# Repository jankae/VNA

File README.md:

# 1MHz - 6GHz VNA

**There is a [new and improved version](https://github.com/jankae/VNA2) of this project under development**

## Motivation
A VNA can be very helpful for RF experiments so I decided to build one for my next project. I already own a [pocketVNA](https://pocketvna.com/), however I found some issues with it and didn't use it very often:
* High thermal drift: you have to leave it running for 30-45 minutes before using it
* Low sweep speed: Especially with averaging enabled, a sweep can take a few minutes
* Ports are not 50 Ohm terminated, see also discussion [here](https://www.eevblog.com/forum/rf-microwave/pocketvna-any-idea-what-its-like/msg1220143/#msg1220143)

There already are some other DIY VNA projects online, especially [these](https://hforsten.com/cheap-homemade-30-mhz-6-ghz-vector-network-analyzer.html) [two](http://www.yl3akb.lv/content/vna_v2/vna_v2.php) served as inspiration. Especially the first link also explains some general concepts of a VNA, what it is used for, how it works and some compromises when choosing a hardware architecture.

## Design goals
* 1MHz to 6GHz usable frequency range. Both limits are essentially set by the specs of affordable RF ICs.
* Reasonable fast sweep speed
* No display, instead the data is send via USB to a PC. Generally, I prefer standalone devices but it seemed not worth the effort here. To be usable, the display would need to be reasonable large and high resolution, also GUI development is faster/easier on a PC than on a µC.
* BOM cost reduction is *not* the primary goal. A project like this takes several month and its a one-off device, slightly higher than absolutely necessary part costs are not an issue.
* Learn more about the challenges in RF designs.

## How does it work?

* The main clock source is an Si5351C, providing all the required clocks for the different blocks. It also serves as the stimulus source for frequencies below 25MHz. Its own reference clock is either a 26MHz crystal or an external 10MHz signal.
* The stimulus source for frequencies above 25MHz is a MAX2871. Its output signal is slightly filtered to reduce the amount of harmonics.
* The stimulus signal power can be adjusted between approximately -42 and -10dbm with a digital attenuator (F1958).
* After the amplifier(TRF37A73) the signal is split and the weaker part of it fed into the reference receiver.
* The stronger part of the signal can be routed to either port. In each signal path, two RF switches are used in series to achieve higher isolation between the ports.
* Instead of directional couplers, resistive return-loss-bridges are used (easier to implement for wide bandwidth).
* Both ports have completely separated receive paths. This increases BOM cost but allows measuring two parameters at once (S11 and S21 or S22 and S12). It also avoid potential isolation issues that could arise if the receive paths would merge into a single mixer/ADC.
* Each receiver consists of two down-convert mixers. The 1.IF sits at 60MHz, the 2.IF 250kHz.
* The ADCs are sampling the final IF with 16bit@1MHz.
* The acquisition and control of the PLLs, switches, attenuator etc. is handled by a Spartan 6 FPGA. This allows for nearly instant switching of the measurement frequency, only limited by the settling time of the PLLs.

## PCB Layout
The signal path can also be followed on the PCB (the attuator is replaced by a wire bridge in this picture because I damaged the IC during soldering):

* I limited myself to 10x10cm, because larger 4-Layer PCBs are getting a bit more expensive at the typical manufacturers. This was a mistake because it meant that certain sections had to move closer together. Especially the distance between the HF Source and the 1.Mixer of Port 1 is not sufficient, resulting in less than optimal isolation.
* The individual sections are divided by strips of exposed GND. The aluminium case touches all the exposed copper and further improves shielding. I expected the shielding to be better than it turned out, this is another reason why I put sections close to each other that really should be some distance apart.
* For some reason I didn't check the final design carefully enough before ordering and didn't have enough GND vias in quite a few areas. This probably degrades overall performance but I am not going to reorder (and solder!) a new PCB.

### Some hardware-related points worth noting
* There is a lot of local voltage regulation to prevent coupling of supply noise between the sections. In total there are 14 different supply rails (although most of them are at 3.3V or 5V).
* The triple Buck converter for stepping down the main 12V input rail to 6V/3V3 and 1V8 has a synchronisation feature. The synchronization pin was connected to the FPGA in order to sync the converter to the ADC sampling rate and prevent switching noise from being measured. I ended up having to cut that trace because the Spartan 6 switches its pins to pullups while being configured from the ISE IDE. This caused the buck converter to stop and the board to lose power. Note that the HSWAPEN pin only affects the pullups when configuring from the *Flash* not from the IDE. See also [this](https://forums.xilinx.com/t5/Spartan-Family-FPGAs-Archived/Spartan-6-pull-ups-during-SPI-indirect-programming-using/td-p/201743) issue. The missing synchronisation ended up not being a problem as the buck converter frequency is far enough away from the final IF.
* Due to 16bit resolution at 1MSPS, the ADCs need a fast SPI interface. Initially I used a 100MHz SPI clock and this worked well for the port 1 and the reference ADC but didn't work with the port 2 ADC (it is farther away from the FPGA thus the traces were longer). Decreasing the SPI clock to about 70MHz solved the issue while still being fast enough for the ADCs.
* The LTC5510 mixers and MAX2871 PLLs get warm (overall power consumption is about 6W, most of it dissipated in these ICs), they reached up to 70°C with an ambient temperature of 25°C. I changed the aluminium shielding design to extend down to these ICs and also serve as a heatsink. This reduced the maximum temperature by about 20°C.

## The shielding

The shielding serves multiple purposes:
* Providing RF isolation between different sections
* Improving EMI/EMC
* Serving as a case for the device, preventing shorts on the PCB when used on the bench
* Cooling (the black rectangles on the left aluminium part are adhesive cooling pads and touch the top of some ICs)
* It was CNC-machined out of 6mm aluminium. Being able to use a CNC mill, I wasn't restricted to right angles and optimised the shielding to allow for a smaller board.

## PC Software

* Written in Qt. This was my first PC software with a GUI and it took a while (and many lines of code that were rewritten a lot) to understand the concepts. While certainly not optimal, the result is absolutely usable for me.
* Flexible display of measurements in charts (Smithchart/Bodeplot). Each chart can be assigned a number of traces (e.i. plot S22 and S11 in one smithchart). The charts can be resized, moved, deleted or split into more charts.
* Import/export of touchstone files up to 4 ports. This allows saving measurements and also comparing the current measurement with others.
* Rudimentary marker system to read S-parameters at any frequency.
* Full control over start/center/stop frequencies, span, IF bandwidth, number of points, stimulus power level, ...
* SOLT calibration with fully customizable calibration kit (either from coefficients or touchstone measurements):

* Manually control of the hardware components (helpful for hardware debugging or using the device as a simple signal source):

## How well does it work?
I am really not that sure, as I have no RF equipment to compare it to. A VNA can only be as good as the calibration kit and the only calibration kit I have is the on that came with the pocketVNA, which does not have any calibration coefficients. Why is that a problem? No calibration kit is perfect and the coefficients allow the VNA to take the imperfections into account. Without the coefficients these imperfections will be propagated to the measurements. As calibration kits with coefficients easily cost more than this whole project (at least the ones I could find) this situation will probably not change soon.

That being said, here are a few measurements:
* Isolation between ports with (green) and without (red) shielding (1MHz to 6GHz, 501 points, 100Hz IF bandwidth, both ports terminated into 50 Ohm):
  * S12:
  
  * S21:
  
  * Below about 1GHz the noise floor is the actual noise floor of the ADC. Above 1GHz more and more signal leaks into the other port. This leakage is a bit worse at port 1 (S12) because the HF source is placed close to the port 1 mixers. The shielding improves the isolation somewhat but not to the extend I had hoped. Interestingly there are some peaks in the isolation sweep when the shielding is used. My best guess is that they are caused by the cavities in the shielding acting as waveguides. I am hoping to improve the shielding by adding RF absorbers to some parts of the aluminium.
* The cavity bandpass filter from [this](https://github.com/jankae/SpectrumAnalyzer) project (1.9GHz to 2.3GHz, 501 points, 1kHz IF bandwidth):
 
* A WLAN antenna that seems to be somewhat reasonable matched between 2.3GHz and 2.6GHz:

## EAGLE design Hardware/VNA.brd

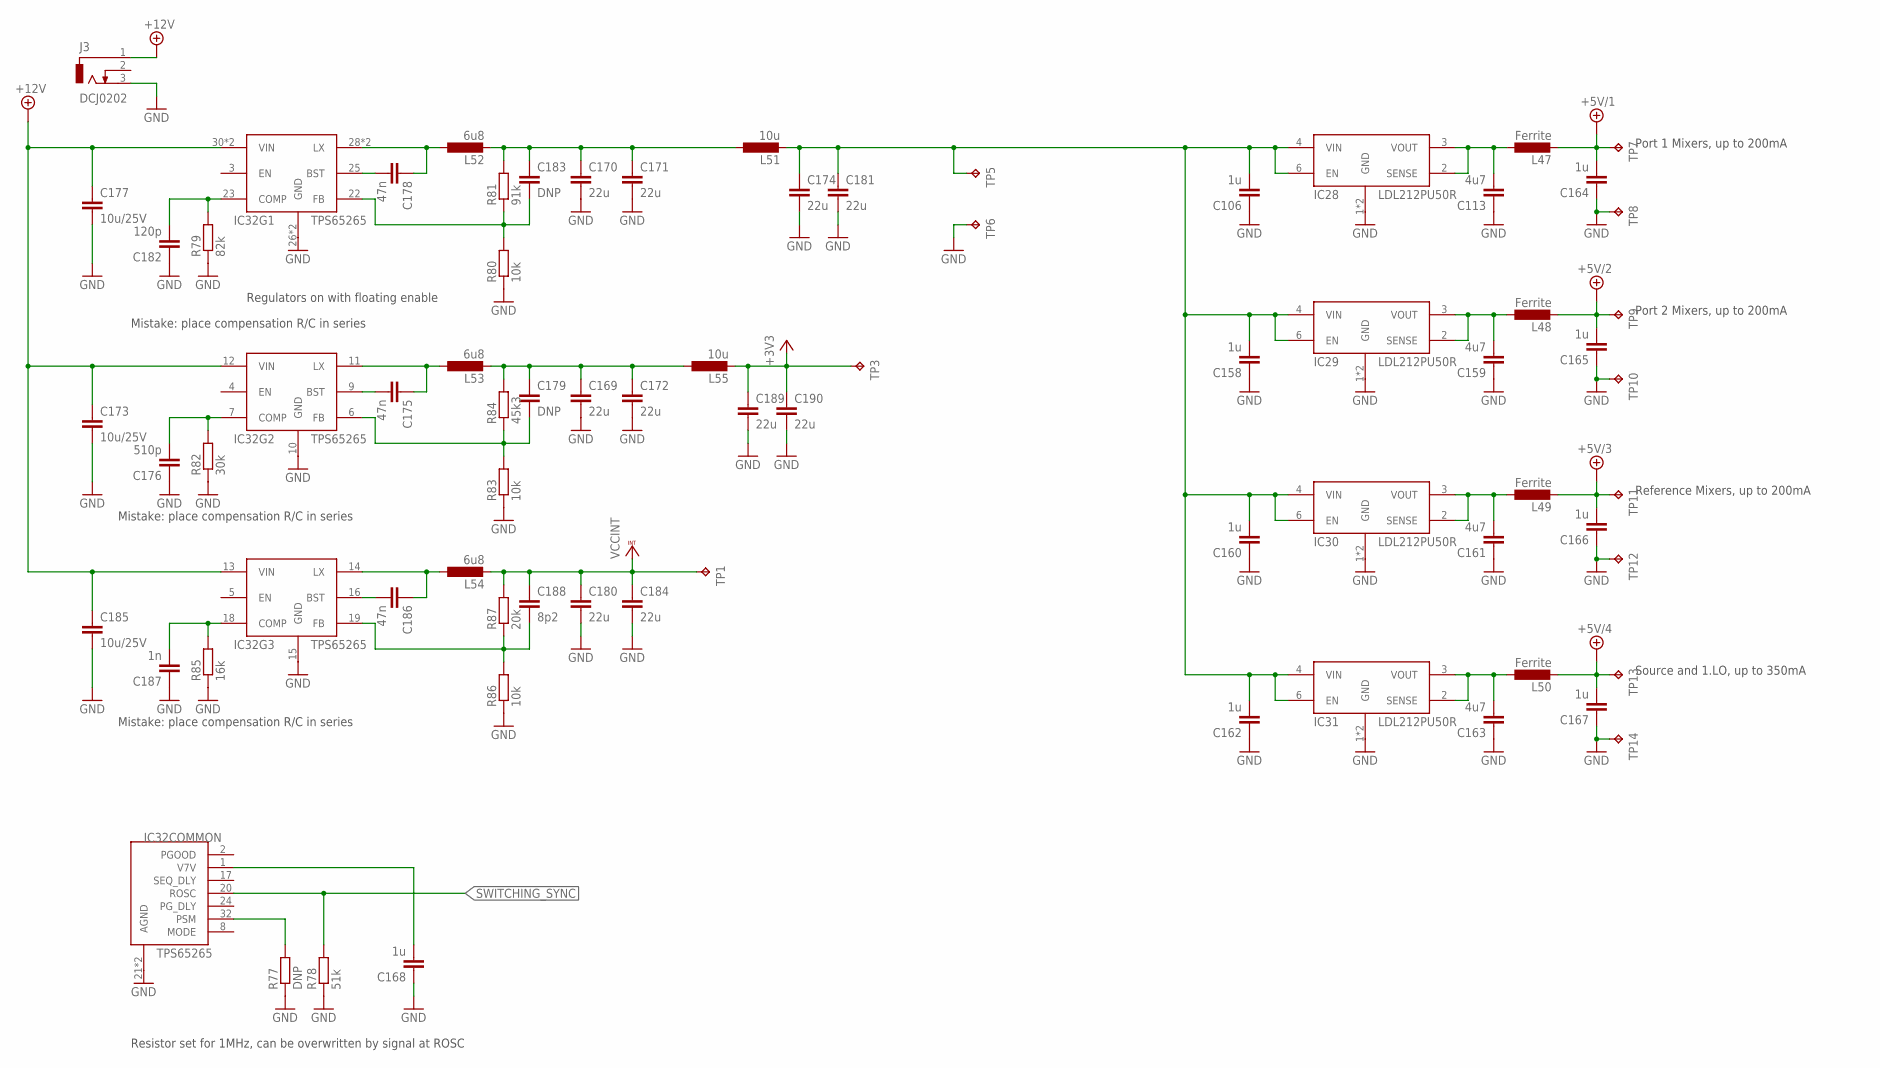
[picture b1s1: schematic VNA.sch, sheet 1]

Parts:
C106, C158, C160, C162, C164, C165, C166, C167, C168: 1u; C0603
C113, C159, C161, C163: 4u7; C0603
C169, C170, C171, C172, C174, C180, C181, C184, C189, C190: 22u; C1206
C173, C177, C185: 10u/25V; C1206
C175, C178, C186: 47n; C0603
C176: 510p; C0603
C179, C183: DNP; C0603
C182: 120p; C0603
C187: 1n; C0603
C188: 8p2; C0603
IC28, IC29, IC30, IC31: LDL212PU50R; SON95P300X300X100-7T170X240N
IC32: TPS65265; QFN50P500X500X100-33T345N
J3: DCJ0202
L47, L48, L49, L50: Ferrite; R0603
L51, L55: 10u; SRN5040
L52, L53, L54: 6u8; SRN5040
R77: DNP; R0603
R78: 51k; R0603
R79: 82k; R0603
R80, R83, R86: 10k; R0603
R81: 91k; R0603
R82: 30k; R0603
R84: 45k3; R0603
R85: 16k; R0603
R87: 20k; R0603
TP1, TP3, TP5, TP6, TP7, TP8, TP9, TP10, TP11, TP12, TP13, TP14: TPB1,27; B1,27

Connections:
+3V3: C189.1, C190.1, L55.P$2 (2), TP3.TP; also elsewhere on the board
+5V/1: C164.2, L47.2, TP7.TP; also elsewhere on the board
+5V/2: C165.2, L48.2, TP9.TP; also elsewhere on the board
+5V/3: C166.2, L49.2, TP11.TP; also elsewhere on the board
+5V/4: C167.2, L50.2, TP13.TP; also elsewhere on the board
+12V: C173.1, C177.1, C185.1, IC32.12 (VIN), IC32.13 (VIN), IC32.30 (VIN), IC32.31 (VIN), J3.1
GND: C106.1, C113.1, C158.1, C159.1, C160.1, C161.1, C162.1, C163.1, C164.1, C165.1, C166.1, C167.1, C168.1, C169.2, C170.2, C171.2, C172.2, C173.2, C174.2, C176.1, C177.2, C180.2, C181.2, C182.1, C184.2, C185.2, C187.1, C189.2, C190.2, IC28.1 (GND), IC28.7 (GND), IC29.1 (GND), IC29.7 (GND), IC30.1 (GND), IC30.7 (GND), IC31.1 (GND), IC31.7 (GND), IC32.10 (GND), IC32.15 (GND), IC32.21 (AGND), IC32.26 (GND), IC32.27 (GND), IC32.33 (AGND), J3.3, R77.1, R78.1, R79.1, R80.1, R82.1, R83.1, R85.1, R86.1, TP6.TP, TP8.TP, TP10.TP, TP12.TP, TP14.TP; also elsewhere on the board
unnamed: C113.2, IC28.2 (SENSE), IC28.3 (VOUT), L47.1
unnamed: C159.2, IC29.2 (SENSE), IC29.3 (VOUT), L48.1
unnamed: C168.2, IC32.1 (V7V)
unnamed: C106.2, C158.2, C160.2, C162.2, C174.1, C181.1, IC28.4 (VIN), IC28.6 (EN), IC29.4 (VIN), IC29.6 (EN), IC30.4 (VIN), IC30.6 (EN), IC31.4 (VIN), IC31.6 (EN), L51.P$2 (2), TP5.TP
unnamed: C161.2, IC30.2 (SENSE), IC30.3 (VOUT), L49.1
unnamed: C163.2, IC31.2 (SENSE), IC31.3 (VOUT), L50.1
unnamed: IC32.32 (PSM), R77.2
unnamed: C178.2, IC32.25 (BST)
unnamed: C178.1, IC32.28 (LX), IC32.29 (LX), L52.P$1 (1)
unnamed: C175.2, IC32.9 (BST)
unnamed: C175.1, IC32.11 (LX), L53.P$1 (1)
unnamed: C176.2, IC32.7 (COMP), R82.2
unnamed: C182.2, IC32.23 (COMP), R79.2
unnamed: C183.2, IC32.22 (FB), R80.2, R81.1
unnamed: C170.1, C171.1, C183.1, L51.P$1 (1), L52.P$2 (2), R81.2
unnamed: C179.2, IC32.6 (FB), R83.2, R84.1
unnamed: C169.1, C172.1, C179.1, L53.P$2 (2), L55.P$1 (1), R84.2
unnamed: C186.2, IC32.16 (BST)
unnamed: C186.1, IC32.14 (LX), L54.P$1 (1)
unnamed: C187.2, IC32.18 (COMP), R85.2
unnamed: C188.2, IC32.19 (FB), R86.2, R87.1
SWITCHING_SYNC: IC32.20 (ROSC), R78.2; also elsewhere on the board
VCCINT: C180.1, C184.1, C188.1, L54.P$2 (2), R87.2, TP1.TP; also elsewhere on the board

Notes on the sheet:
Port 1 Mixers, up to 200mA
Port 2 Mixers, up to 200mA
Reference Mixers, up to 200mA
Source and 1.LO, up to 350mA
Resistor set for 1MHz, can be overwritten by signal at ROSC
Regulators on with floating enable
Mistake: place compensation R/C in series

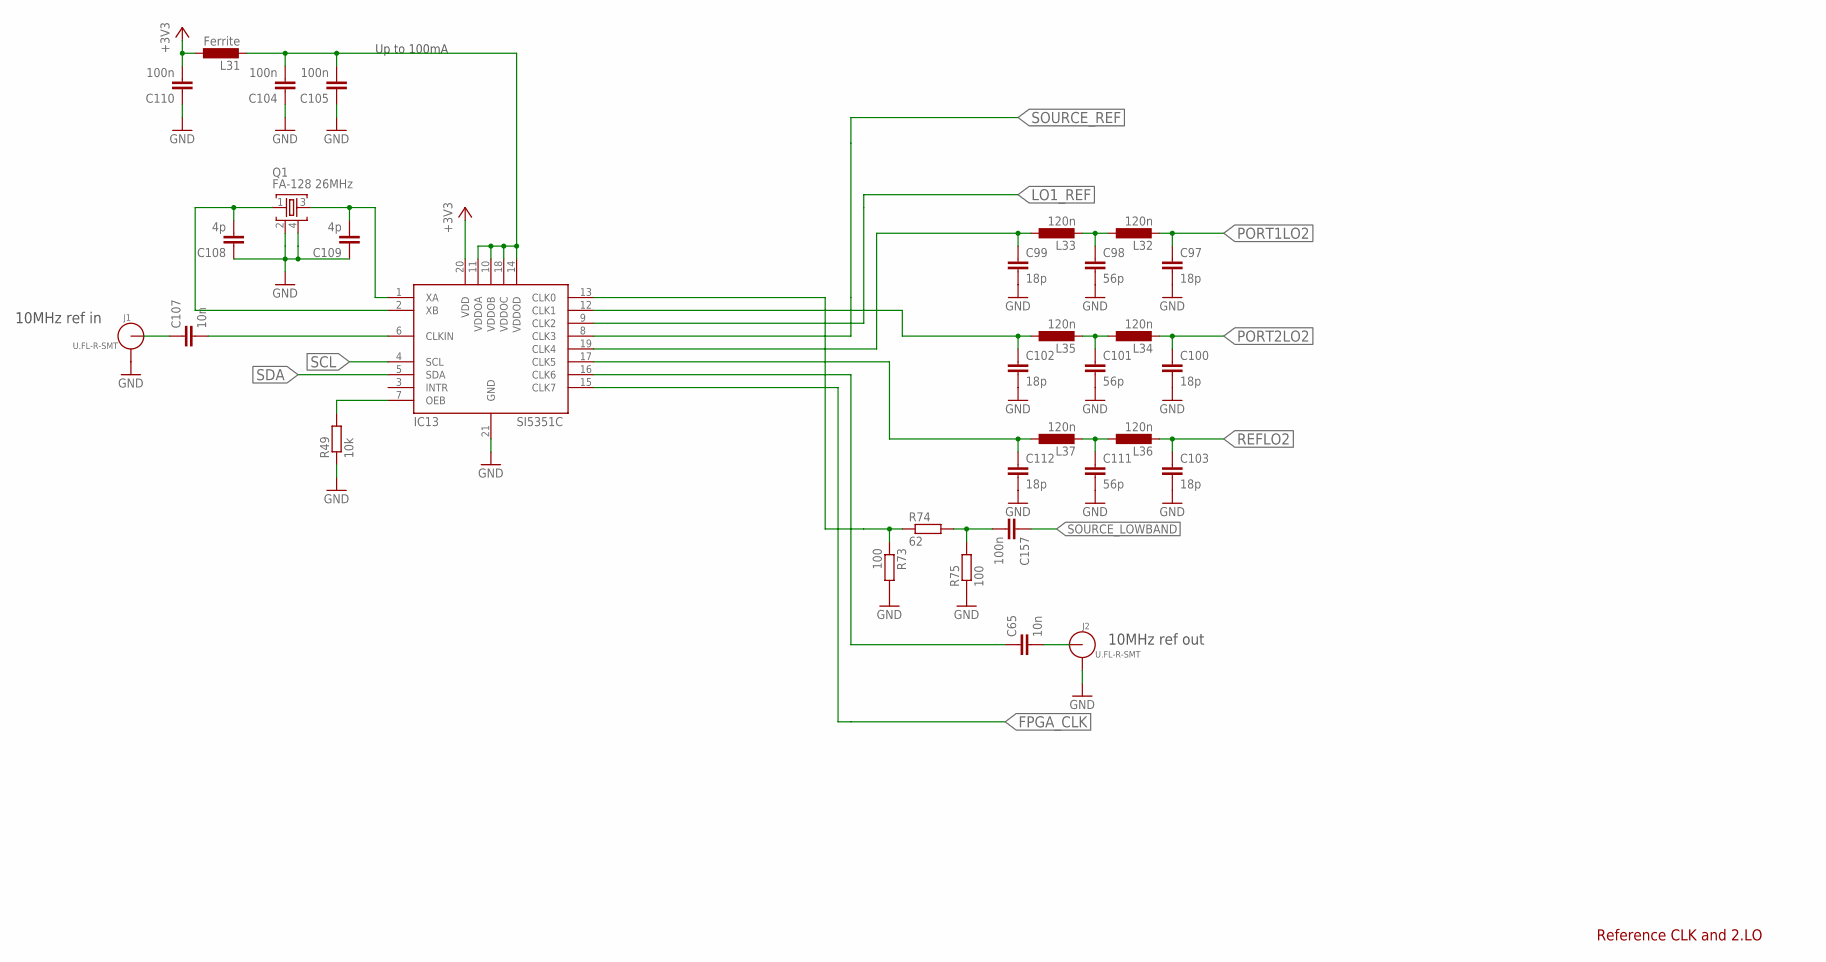
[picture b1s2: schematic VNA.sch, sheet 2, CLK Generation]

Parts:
C65, C107: 10n; C0603
C97, C99, C100, C102, C103, C112: 18p; C0603
C98, C101, C111: 56p; C0603
C104, C105, C110, C157: 100n; C0603
C108, C109: 4p; C0603
IC13: SI5351C; QFN50P400X400X90-21T270N
J1, J2: U.FL-R-SMT; U.FL_SMT
L31: Ferrite; R0603
L32, L33, L34, L35, L36, L37: 120n; R0603
Q1: FA-128 26MHz; FA-128
R49: 10k; R0603
R73, R75: 100; R0603
R74: 62; R0603

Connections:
+3V3: C110.2, IC13.20 (VDD), L31.1; also elsewhere on the board
FPGA_CLK: IC13.15 (CLK7); also elsewhere on the board
GND: C97.2, C98.2, C99.2, C100.2, C101.2, C102.2, C103.2, C104.1, C105.1, C108.1, C109.1, C110.1, C111.2, C112.2, IC13.21 (GND), J1.GND1, J1.GND2, J2.GND1, J2.GND2, Q1.2, Q1.4, R49.1, R73.2, R75.1; also elsewhere on the board
LO1_REF: IC13.9 (CLK2); also elsewhere on the board
unnamed: C65.2, J2.SIG (ANT)
unnamed: C98.1, L32.1, L33.2
unnamed: C101.1, L34.1, L35.2
unnamed: C102.1, IC13.12 (CLK1), L35.1
unnamed: C111.1, L36.1, L37.2
unnamed: C99.1, IC13.19 (CLK4), L33.1
unnamed: C65.1, IC13.16 (CLK6)
unnamed: C107.1, J1.SIG (ANT)
unnamed: C107.2, IC13.6 (CLKIN)
unnamed: C104.2, C105.2, IC13.10 (VDDOB), IC13.11 (VDDOA), IC13.14 (VDDOD), IC13.18 (VDDOC), L31.2
unnamed: IC13.7 (OEB), R49.2
unnamed: C109.2, IC13.1 (XA), Q1.3
unnamed: C108.2, IC13.2 (XB), Q1.1
unnamed: IC13.13 (CLK0), R73.1, R74.1
unnamed: C157.2, R74.2, R75.2
unnamed: C112.1, IC13.17 (CLK5), L37.1
PORT1LO2: C97.1, L32.2; also elsewhere on the board
PORT2LO2: C100.1, L34.2; also elsewhere on the board
REFLO2: C103.1, L36.2; also elsewhere on the board
SCL: IC13.4 (SCL); also elsewhere on the board
SDA: IC13.5 (SDA); also elsewhere on the board
SOURCE_LOWBAND: C157.1; also elsewhere on the board
SOURCE_REF: IC13.8 (CLK3); also elsewhere on the board

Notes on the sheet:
Reference CLK and 2.LO
10MHz ref in
10MHz ref out
Up to 100mA

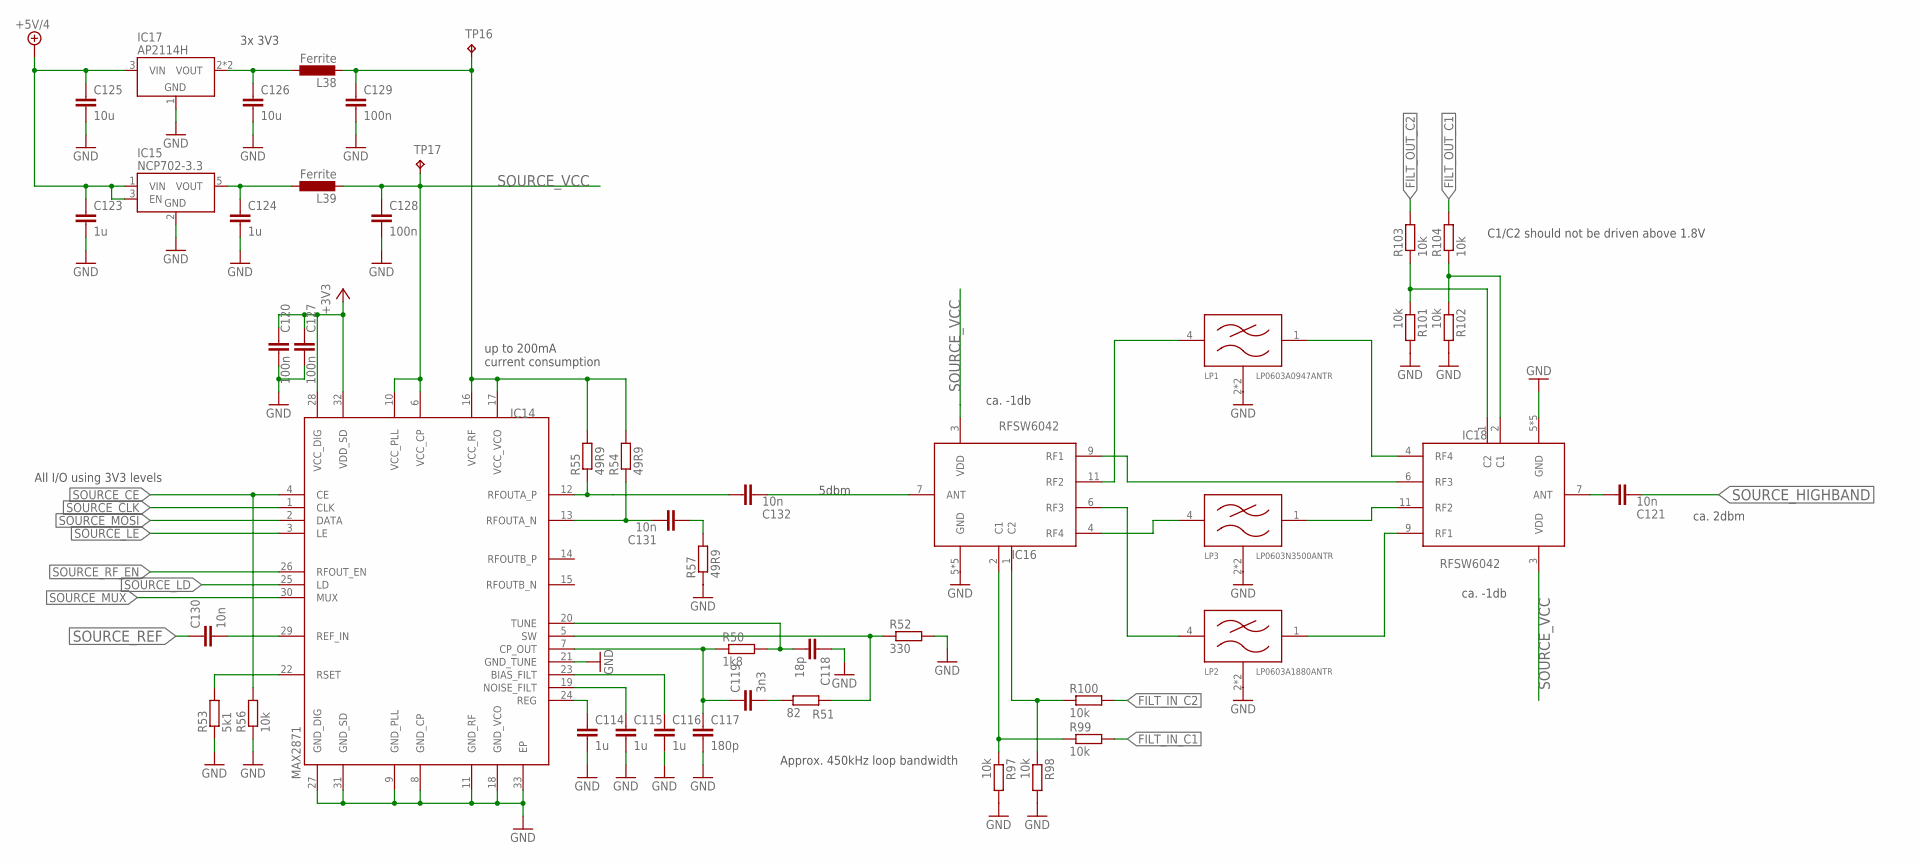
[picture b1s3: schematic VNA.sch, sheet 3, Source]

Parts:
C114, C115, C116, C123, C124: 1u; C0603
C117: 180p; C0603
C118: 18p; C0603
C119: 3n3; C0603
C120, C127, C128, C129: 100n; C0603
C121, C130, C131, C132: 10n; C0603
C125, C126: 10u; C1206
IC14: MAX2871; QFN50P500X500X80-33T310
IC15: NCP702-3.3; SOT95P240X110-5
IC16, IC18: RFSW6042; QFN40P180X180X55-13T76N
IC17: AP2114H; SOT230P700X180-4
L38, L39: Ferrite; R0603
LP1: LP0603A0947ANTR; FILTRDFN160X84X70-4N
LP2: LP0603A1880ANTR; FILTRDFN160X84X70-4N
LP3: LP0603N3500ANTR; FILTRDFN160X84X70-4N
R50: 1k8; R0603
R51: 82; R0603
R52: 330; R0603
R53: 5k1; R0603
R54, R55, R57: 49R9; R0603
R56, R97, R98, R99, R100, R101, R102, R103, R104: 10k; R0603
TP16, TP17: TPB1,27; B1,27

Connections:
+3V3: C120.1, C127.1, IC14.28 (VCC_DIG), IC14.32 (VDD_SD); also elsewhere on the board
+5V/4: C123.1, C125.1, IC15.1 (VIN), IC15.3 (EN), IC17.3 (VIN); also elsewhere on the board
FILT_IN_C1: R99.2; also elsewhere on the board
FILT_IN_C2: R100.2; also elsewhere on the board
FILT_OUT_C1: R104.2; also elsewhere on the board
FILT_OUT_C2: R103.2; also elsewhere on the board
GND: C114.2, C115.2, C116.2, C117.2, C118.1, C120.2, C123.2, C124.2, C125.2, C126.2, C127.2, C128.2, C129.2, IC14.8 (GND_CP), IC14.9 (GND_PLL), IC14.11 (GND_RF), IC14.18 (GND_VCO), IC14.21 (GND_TUNE), IC14.27 (GND_DIG), IC14.31 (GND_SD), IC14.33 (EP), IC15.2 (GND), IC16.5 (GND), IC16.8 (GND), IC16.10 (GND), IC16.12 (GND), IC16.13 (GND), IC17.1 (GND), IC18.5 (GND), IC18.8 (GND), IC18.10 (GND), IC18.12 (GND), IC18.13 (GND), LP1.2 (GND), LP1.3 (GND), LP2.2 (GND), LP2.3 (GND), LP3.2 (GND), LP3.3 (GND), R52.2, R53.1, R56.1, R57.1, R97.2, R98.2, R101.2, R102.2; also elsewhere on the board
unnamed: C118.2, IC14.20 (TUNE), R50.2
unnamed: C117.1, C119.1, IC14.7 (CP_OUT), R50.1
unnamed: C114.1, IC14.24 (REG)
unnamed: C115.1, IC14.19 (NOISE_FILT)
unnamed: C116.1, IC14.23 (BIAS_FILT)
unnamed: C119.2, R51.1
unnamed: IC14.5 (SW), R51.2, R52.1
unnamed: IC14.22 (RSET), R53.2
unnamed: C129.1, IC14.16 (VCC_RF), IC14.17 (VCC_VCO), L38.2, R54.2, R55.2, TP16.TP
unnamed: C130.2, IC14.29 (REF_IN)
unnamed: C132.1, IC14.12 (RFOUTA_P), R55.1
unnamed: C131.2, IC14.13 (RFOUTA_N), R54.1
unnamed: C131.1, R57.2
unnamed: C132.2, IC16.7 (ANT)
unnamed: IC16.9 (RF1), IC18.6 (RF3)
unnamed: IC16.11 (RF2), LP1.4 (IN)
unnamed: IC18.4 (RF4), LP1.1 (OUT)
unnamed: IC18.11 (RF2), LP3.1 (OUT)
unnamed: IC18.9 (RF1), LP2.1 (OUT)
unnamed: IC16.6 (RF3), LP2.4 (IN)
unnamed: IC16.4 (RF4), LP3.4 (IN)
unnamed: C126.1, IC17.2 (VOUT), IC17.4 (VOUT), L38.1
unnamed: C124.1, IC15.5 (VOUT), L39.1
unnamed: C121.1, IC18.7 (ANT)
unnamed: IC16.2 (C1), R97.1, R99.1
unnamed: IC16.1 (C2), R98.1, R100.1
unnamed: IC18.1 (C2), R101.1, R103.1
unnamed: IC18.2 (C1), R102.1, R104.1
SOURCE_CE: IC14.4 (CE), R56.2; also elsewhere on the board
SOURCE_CLK: IC14.1 (CLK); also elsewhere on the board
SOURCE_HIGHBAND: C121.2; also elsewhere on the board
SOURCE_LD: IC14.25 (LD); also elsewhere on the board
SOURCE_LE: IC14.3 (LE); also elsewhere on the board
SOURCE_MOSI: IC14.2 (DATA); also elsewhere on the board
SOURCE_MUX: IC14.30 (MUX); also elsewhere on the board
SOURCE_REF: C130.1; also elsewhere on the board
SOURCE_RF_EN: IC14.26 (RFOUT_EN); also elsewhere on the board
SOURCE_VCC: C128.1, IC14.6 (VCC_CP), IC14.10 (VCC_PLL), IC16.3 (VDD), IC18.3 (VDD), L39.2, TP17.TP

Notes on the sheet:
up to 200mA current consumption
All I/O using 3V3 levels
3x 3V3
Approx. 450kHz loop bandwidth
5dbm
ca. -1db
ca. 2dbm
C1/C2 should not be driven above 1.8V

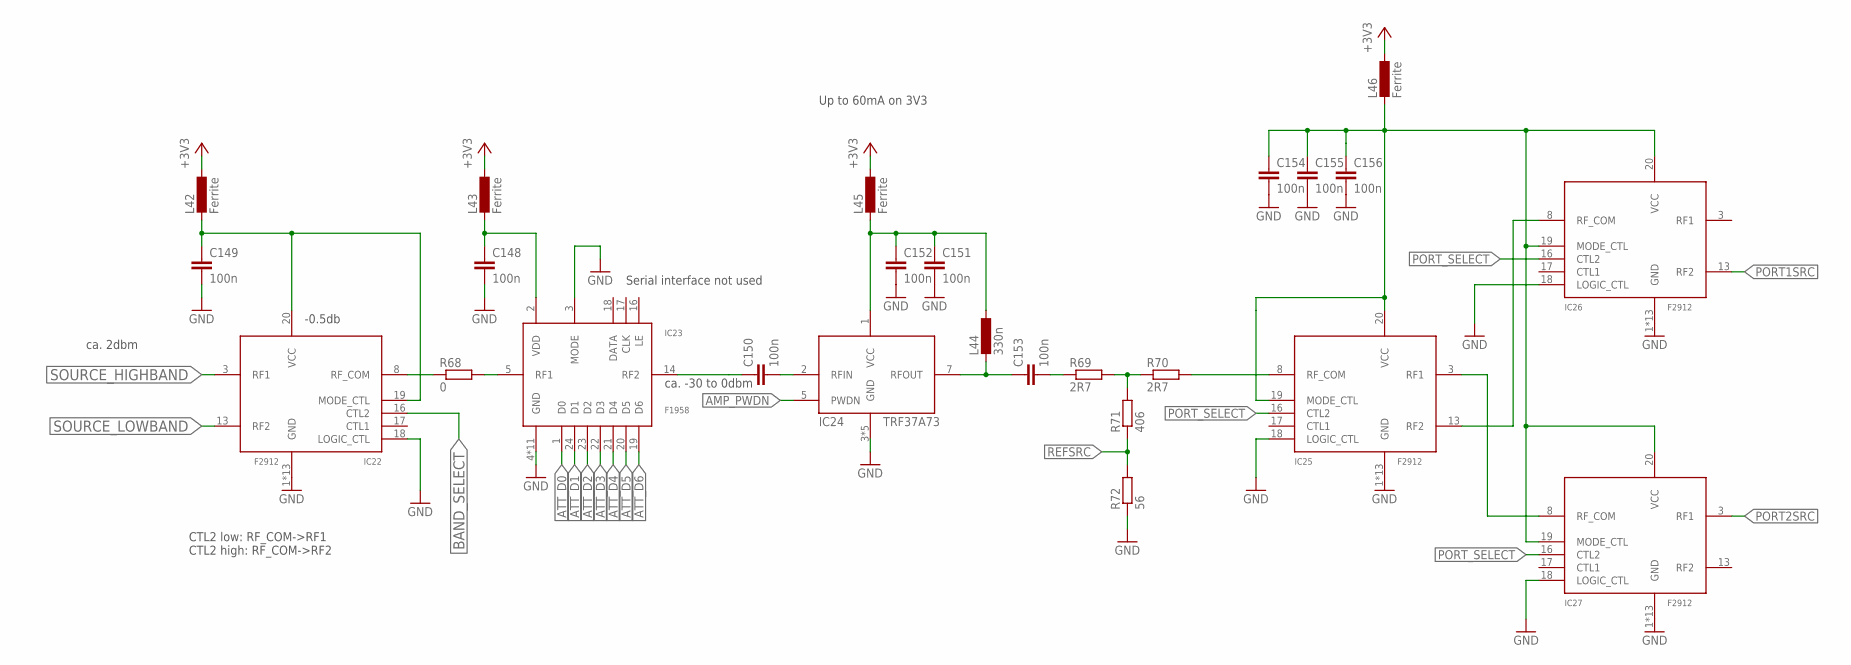
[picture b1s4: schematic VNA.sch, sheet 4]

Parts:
C148, C149, C150, C151, C152, C153, C154, C155, C156: 100n; C0603
IC22, IC25, IC26, IC27: F2912; QFN50P400X400X75-21T206
IC23: F1958; QFN50P400X400X75-25T270
IC24: TRF37A73; SON50P200X200X80-9T90X160N
L42, L43, L45, L46: Ferrite; R0603
L44: 330n; R0603
R68: 0; R0603
R69, R70: 2R7; R0603
R71: 406; R0603
R72: 56; R0603

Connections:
+3V3: L42.1, L43.1, L45.1, L46.1; also elsewhere on the board
AMP_PWDN: IC24.5 (PWDN); also elsewhere on the board
ATT_D0: IC23.1 (D0); also elsewhere on the board
ATT_D1: IC23.24 (D1); also elsewhere on the board
ATT_D2: IC23.23 (D2); also elsewhere on the board
ATT_D3: IC23.22 (D3); also elsewhere on the board
ATT_D4: IC23.21 (D4); also elsewhere on the board
ATT_D5: IC23.20 (D5); also elsewhere on the board
ATT_D6: IC23.19 (D6); also elsewhere on the board
BAND_SELECT: IC22.16 (CTL2); also elsewhere on the board
GND: C148.2, C149.2, C151.2, C152.2, C154.2, C155.2, C156.2, IC22.1 (GND), IC22.2 (GND), IC22.4 (GND), IC22.5 (GND), IC22.6 (GND), IC22.7 (GND), IC22.9 (GND), IC22.10 (GND), IC22.11 (GND), IC22.12 (GND), IC22.14 (GND), IC22.15 (GND), IC22.18 (LOGIC_CTL), IC22.21 (GND), IC23.3 (MODE), IC23.4 (GND), IC23.6 (GND), IC23.7 (GND), IC23.8 (GND), IC23.9 (GND), IC23.10 (GND), IC23.11 (GND), IC23.12 (GND), IC23.13 (GND), IC23.15 (GND), IC23.25 (GND), IC24.3 (GND), IC24.4 (GND), IC24.6 (GND), IC24.8 (GND), IC24.9 (GND), IC25.1 (GND), IC25.2 (GND), IC25.4 (GND), IC25.5 (GND), IC25.6 (GND), IC25.7 (GND), IC25.9 (GND), IC25.10 (GND), IC25.11 (GND), IC25.12 (GND), IC25.14 (GND), IC25.15 (GND), IC25.18 (LOGIC_CTL), IC25.21 (GND), IC26.1 (GND), IC26.2 (GND), IC26.4 (GND), IC26.5 (GND), IC26.6 (GND), IC26.7 (GND), IC26.9 (GND), IC26.10 (GND), IC26.11 (GND), IC26.12 (GND), IC26.14 (GND), IC26.15 (GND), IC26.18 (LOGIC_CTL), IC26.21 (GND), IC27.1 (GND), IC27.2 (GND), IC27.4 (GND), IC27.5 (GND), IC27.6 (GND), IC27.7 (GND), IC27.9 (GND), IC27.10 (GND), IC27.11 (GND), IC27.12 (GND), IC27.14 (GND), IC27.15 (GND), IC27.18 (LOGIC_CTL), IC27.21 (GND), R72.1; also elsewhere on the board
unnamed: C149.1, IC22.19 (MODE_CTL), IC22.20 (VCC), L42.2
unnamed: IC22.8 (RF_COM), R68.1
unnamed: C148.1, IC23.2 (VDD), L43.2
unnamed: C150.1, IC23.14 (RF2)
unnamed: C150.2, IC24.2 (RFIN)
unnamed: C153.1, IC24.7 (RFOUT), L44.2
unnamed: C153.2, R69.1
unnamed: IC25.8 (RF_COM), R70.2
unnamed: C151.1, C152.1, IC24.1 (VCC), L44.1, L45.2
unnamed: R69.2, R70.1, R71.2
unnamed: IC25.13 (RF2), IC26.8 (RF_COM)
unnamed: IC25.3 (RF1), IC27.8 (RF_COM)
unnamed: C154.1, C155.1, C156.1, IC25.19 (MODE_CTL), IC25.20 (VCC), IC26.19 (MODE_CTL), IC26.20 (VCC), IC27.19 (MODE_CTL), IC27.20 (VCC), L46.2
unnamed: IC23.5 (RF1), R68.2
PORT1SRC: IC26.13 (RF2); also elsewhere on the board
PORT2SRC: IC27.3 (RF1); also elsewhere on the board
PORT_SELECT: IC25.16 (CTL2), IC26.16 (CTL2), IC27.16 (CTL2); also elsewhere on the board
REFSRC: R71.1, R72.2; also elsewhere on the board
SOURCE_HIGHBAND: IC22.3 (RF1); also elsewhere on the board
SOURCE_LOWBAND: IC22.13 (RF2); also elsewhere on the board

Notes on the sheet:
CTL2 low: RF_COM->RF1 CTL2 high: RF_COM->RF2
Serial interface not used
ca. 2dbm
-0.5db
ca. -30 to 0dbm
Up to 60mA on 3V3

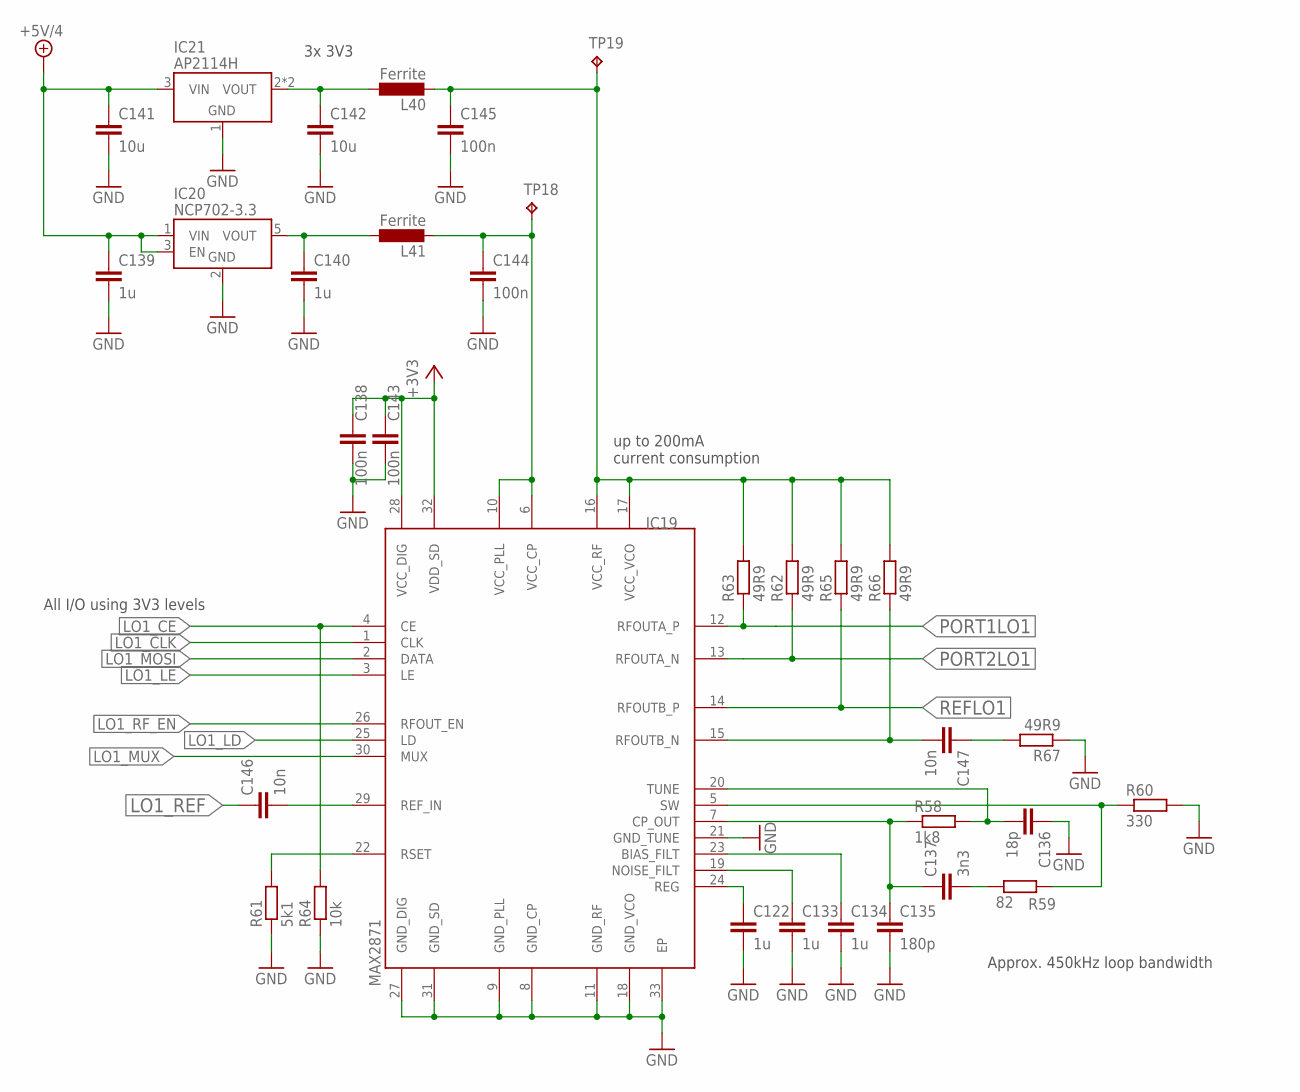
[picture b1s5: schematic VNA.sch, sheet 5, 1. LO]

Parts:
C122, C133, C134, C139, C140: 1u; C0603
C135: 180p; C0603
C136: 18p; C0603
C137: 3n3; C0603
C138, C143, C144, C145: 100n; C0603
C141, C142: 10u; C1206
C146, C147: 10n; C0603
IC19: MAX2871; QFN50P500X500X80-33T310
IC20: NCP702-3.3; SOT95P240X110-5
IC21: AP2114H; SOT230P700X180-4
L40, L41: Ferrite; R0603
R58: 1k8; R0603
R59: 82; R0603
R60: 330; R0603
R61: 5k1; R0603
R62, R63, R65, R66, R67: 49R9; R0603
R64: 10k; R0603
TP18, TP19: TPB1,27; B1,27

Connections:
+3V3: C138.1, C143.1, IC19.28 (VCC_DIG), IC19.32 (VDD_SD); also elsewhere on the board
+5V/4: C139.1, C141.1, IC20.1 (VIN), IC20.3 (EN), IC21.3 (VIN); also elsewhere on the board
GND: C122.2, C133.2, C134.2, C135.2, C136.1, C138.2, C139.2, C140.2, C141.2, C142.2, C143.2, C144.2, C145.2, IC19.8 (GND_CP), IC19.9 (GND_PLL), IC19.11 (GND_RF), IC19.18 (GND_VCO), IC19.21 (GND_TUNE), IC19.27 (GND_DIG), IC19.31 (GND_SD), IC19.33 (EP), IC20.2 (GND), IC21.1 (GND), R60.2, R61.1, R64.1, R67.1; also elsewhere on the board
LO1_CE: IC19.4 (CE), R64.2; also elsewhere on the board
LO1_CLK: IC19.1 (CLK); also elsewhere on the board
LO1_LD: IC19.25 (LD); also elsewhere on the board
LO1_LE: IC19.3 (LE); also elsewhere on the board
LO1_MOSI: IC19.2 (DATA); also elsewhere on the board
LO1_MUX: IC19.30 (MUX); also elsewhere on the board
LO1_REF: C146.1; also elsewhere on the board
LO1_RF_EN: IC19.26 (RFOUT_EN); also elsewhere on the board
unnamed: C144.1, IC19.6 (VCC_CP), IC19.10 (VCC_PLL), L41.2, TP18.TP
unnamed: C136.2, IC19.20 (TUNE), R58.2
unnamed: C135.1, C137.1, IC19.7 (CP_OUT), R58.1
unnamed: C122.1, IC19.24 (REG)
unnamed: C133.1, IC19.19 (NOISE_FILT)
unnamed: C134.1, IC19.23 (BIAS_FILT)
unnamed: C137.2, R59.1
unnamed: IC19.5 (SW), R59.2, R60.1
unnamed: IC19.22 (RSET), R61.2
unnamed: C145.1, IC19.16 (VCC_RF), IC19.17 (VCC_VCO), L40.2, R62.2, R63.2, R65.2, R66.2, TP19.TP
unnamed: C146.2, IC19.29 (REF_IN)
unnamed: C147.1, R67.2
unnamed: C142.1, IC21.2 (VOUT), IC21.4 (VOUT), L40.1
unnamed: C140.1, IC20.5 (VOUT), L41.1
unnamed: C147.2, IC19.15 (RFOUTB_N), R66.1
PORT1LO1: IC19.12 (RFOUTA_P), R63.1; also elsewhere on the board
PORT2LO1: IC19.13 (RFOUTA_N), R62.1; also elsewhere on the board
REFLO1: IC19.14 (RFOUTB_P), R65.1; also elsewhere on the board

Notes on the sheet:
up to 200mA current consumption
All I/O using 3V3 levels
3x 3V3
Approx. 450kHz loop bandwidth
